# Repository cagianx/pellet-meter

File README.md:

# pellet-meter

Sensore di livello del pellet a batteria, per stufe. Misura con un sensore ToF
laser la distanza tra il coperchio e la superficie del pellet nella tramoggia,
e la trasmette a Home Assistant via **BLE advertising in formato BTHome v2**,
insieme allo stato della batteria.

Nessuna connessione BLE, nessun Wi-Fi, nessuna integrazione custom: il
dispositivo si risveglia, misura, trasmette un pacchetto di advertising e
torna in deep sleep. Home Assistant lo riconosce da solo.

## Hardware

| | |
|---|---|
| MCU | Seeed XIAO ESP32C6 — USB-C e caricabatterie LiPo integrati, BLE 5 |
| Sensore | VL53L1X (ToF laser, I²C) — misura da ~4 cm, niente zona cieca |
| Alimentazione | LiPo 3,7 V 1000 mAh con circuito di protezione |
| Radio | BLE advertising, BTHome v2 |

Risveglio ogni **10 minuti**. Consumo stimato **~1,3 mAh al giorno**, cioe'
oltre un anno di autonomia teorica — a quel punto conta piu' l'autoscarica
della batteria che il dispositivo. E' una stima: la misura sul banco e'
ancora da fare.

## Stato

| | |
|---|---|
| Schema elettrico | fatto — ERC pulito, netlist verificata; disposizione da curare |
| Firmware | scheletro ESP-IDF che compila, switch RF; misura e BTHome da scrivere |
| Contenitore 3D | modello OpenSCAD parametrico, quote verificate; si incolla sotto il coperchio della tramoggia, quindi capovolto |
| Configurazione Home Assistant | da fare |

Il repo fornisce **il progetto**, non la realizzazione: schema, firmware,
modello del contenitore e configurazione di Home Assistant. Comprare,
saldare, stampare e installare sono attivita' di chi costruisce.

La calibrazione (distanza ↔ percentuale di riempimento) si fa **in Home
Assistant**, non nel firmware: ricalibrare non richiede un reflash.

## Documentazione

Il sito completo — decisioni di progetto, hardware, collegamenti, formato del
pacchetto BTHome, configurazione di Home Assistant — e' pubblicato qui:

**https://cagianx.github.io/pellet-meter/**

Per lavorare sul repo, vedi [CLAUDE.md](CLAUDE.md): contiene i comandi di
verifica e le trappole del formato KiCad incontrate durante lo sviluppo.

## Struttura

```
kicad/        progetto KiCad 10 (schema, librerie di progetto, strumenti)
firmware/     progetto ESP-IDF (C17, target esp32c6)
enclosure/    contenitore parametrico OpenSCAD
tools/        render.sh — immagini per il sito e il README
docs/         sorgenti del sito di documentazione
```

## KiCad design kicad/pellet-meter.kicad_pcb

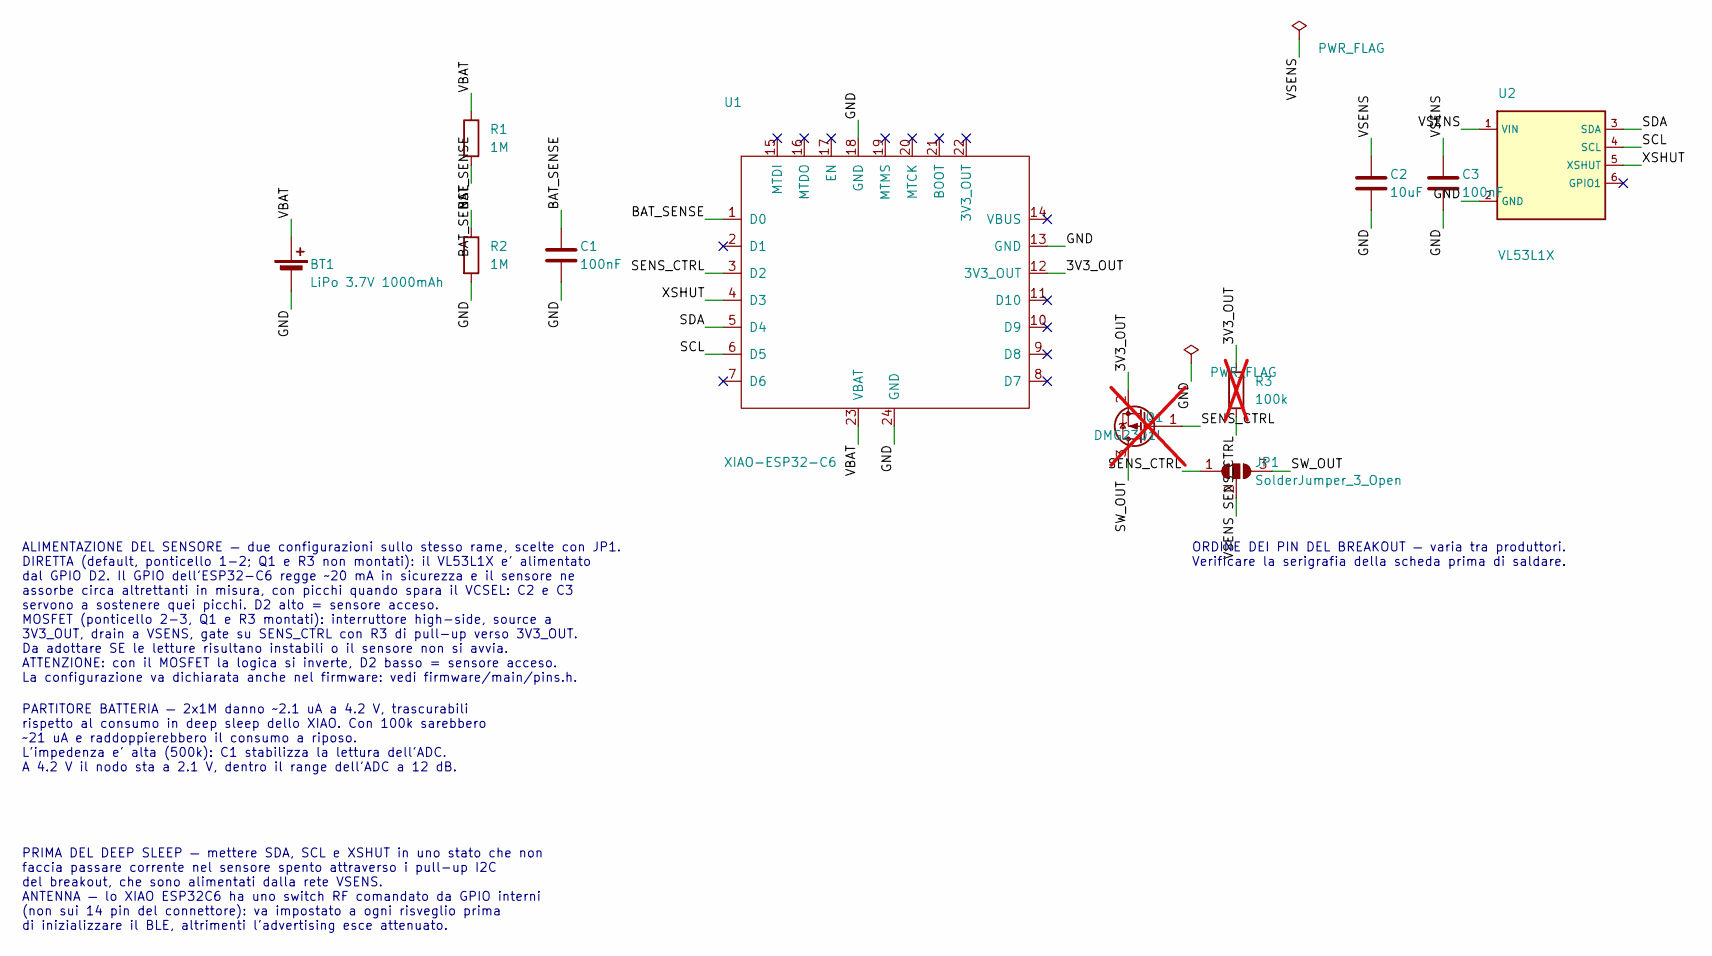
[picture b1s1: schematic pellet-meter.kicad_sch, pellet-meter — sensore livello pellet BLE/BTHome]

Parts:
BT1: LiPo 3.7V 1000mAh; PinHeader_1x02_P2.54mm_Vertical
C1, C3: 100nF; C_Disc_D5.0mm_W2.5mm_P5.00mm
C2: 10uF; CP_Radial_D5.0mm_P2.00mm
JP1: SolderJumper_3_Open; SolderJumper-3_P1.3mm_Open_Pad1.0x1.5mm_NumberLabels
Q1: DMG2301L; SOT-23; not fitted
R1, R2: 1M; R_Axial_DIN0207_L6.3mm_D2.5mm_P7.62mm_Horizontal
R3: 100k; R_Axial_DIN0207_L6.3mm_D2.5mm_P7.62mm_Horizontal; not fitted
U1: XIAO-ESP32-C6; XIAO-ESP32-C6-DIP
U2: VL53L1X; PinHeader_1x06_P2.54mm_Vertical

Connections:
/3V3_OUT: Q1.2 (S), R3.1, U1.12 (3V3_OUT)
/BAT_SENSE: C1.1, R1.2, R2.1, U1.1 (D0)
/GND: BT1.2 (-), C1.2, C2.2, C3.2, R2.2, U1.13 (GND), U1.18 (GND), U1.24 (GND), U2.2 (GND)
/SCL: U1.6 (D5), U2.4 (SCL)
/SDA: U1.5 (D4), U2.3 (SDA)
/SENS_CTRL: JP1.1 (A), Q1.1 (G), R3.2, U1.3 (D2)
/SW_OUT: JP1.3 (B), Q1.3 (D)
/VBAT: BT1.1 (+), R1.1, U1.23 (VBAT)
/VSENS: C2.1, C3.1, JP1.2 (C), U2.1 (VIN)
/XSHUT: U1.4 (D3), U2.5 (XSHUT)

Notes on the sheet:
ALIMENTAZIONE DEL SENSORE — due configurazioni sullo stesso rame, scelte con JP1. DIRETTA (default, ponticello 1-2; Q1 e R3 non montati): il VL53L1X e' alimentato dal GPIO D2. Il GPIO dell'ESP32-C6 regge ~20 mA in sicurezza e il sensore ne assorbe circa altrettanti in misura, con picchi quando spar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
PARTITORE BATTERIA — 2x1M danno ~2.1 uA a 4.2 V, trascurabili rispetto al consumo in deep sleep dello XIAO. Con 100k sarebbero ~21 uA e raddoppierebbero il consumo a riposo. L'impedenza e' alta (500k): C1 stabilizza la lettura dell'ADC. A 4.2 V il nodo sta a 2.1 V, dentro il range dell'ADC a 12 dB.
PRIMA DEL DEEP SLEEP — mettere SDA, SCL e XSHUT in uno stato che non faccia passare corrente nel sensore spento attraverso i pull-up I2C del breakout, che sono alimentati dalla rete VSENS. ANTENNA — lo XIAO ESP32C6 ha uno switch RF comandato da GPIO interni (non sui 14 pin del connettore): va impos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
ORDINE DEI PIN DEL BREAKOUT — varia tra produttori. Verificare la serigrafia della scheda prima di saldare.

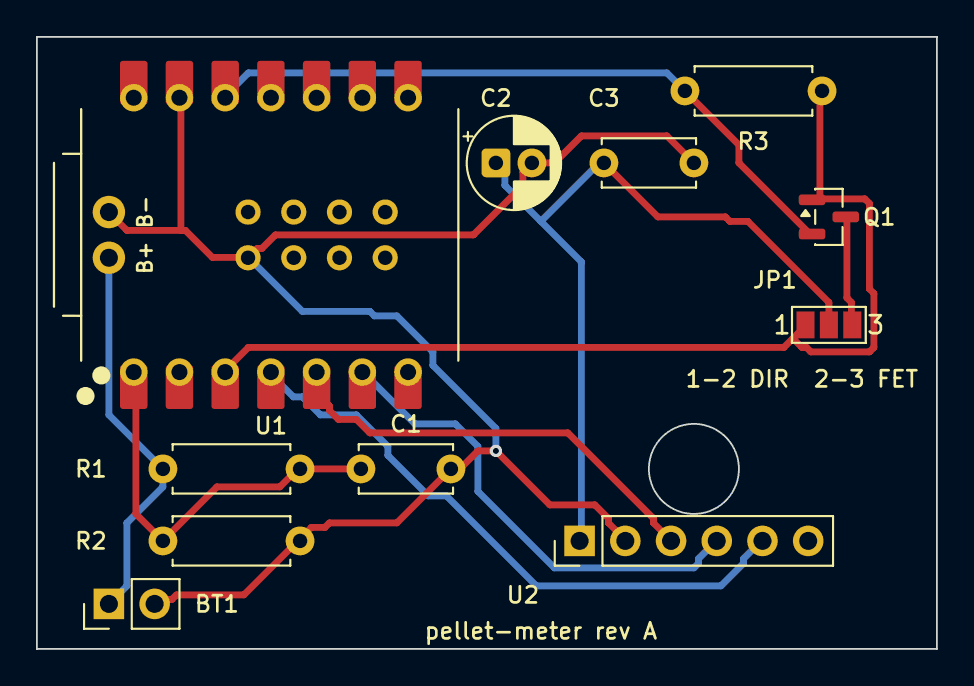
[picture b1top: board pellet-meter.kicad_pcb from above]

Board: 2 copper layers, 50.0 x 34.0 mm, 11 parts (0 on the bottom side), 10 nets.

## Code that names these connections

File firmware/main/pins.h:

// Mappa dei pin. Lo XIAO ESP32C6 stampa sulla scheda i nomi D0..D10, che
// non sono i numeri di GPIO: tradurli a mano in ogni file e' il modo di
// sbagliarne uno. Qui stanno entrambi i nomi, e questa e' l'unica tabella.
//
// Corrispondenza D -> GPIO dal wiki Seeed del XIAO ESP32C6; le reti sono
// quelle dello schema in kicad/pellet-meter.kicad_sch.

#pragma once

#include "driver/gpio.h"
#include "hal/adc_types.h"

// --- Reti dello schema ------------------------------------------------------

// SENS_CTRL: il pin che comanda l'alimentazione del breakout VL53L1X.
#define PIN_SENS_CTRL GPIO_NUM_2 // D2

// Come e' alimentato il sensore. Sul PCB le due configurazioni convivono e
// si scelgono col ponticello JP1 (1-2 diretta, 2-3 a MOSFET); su millefori
// c'e' solo la diretta.
//
//   0  diretta: D2 alimenta il breakout. ALTO = acceso.
//   1  MOSFET:  D2 pilota il gate di Q1, P-MOSFET high-side. BASSO = acceso.
//
// FRA LE DUE LA LOGICA SI INVERTE. E' una scelta esplicita a compile time
// proprio per questo: montare Q1 e dimenticarsene produce un sensore che
// non si accende mai, e sul banco sembra un sensore guasto. Il default e'
// allineato al default del rame, cioe' la configurazione gia' verificata.
#ifndef SENSORE_CON_MOSFET
#define SENSORE_CON_MOSFET 0
#endif

// Livello da mettere su SENS_CTRL per accendere il sensore.
#define SENS_CTRL_ACCESO (SENSORE_CON_MOSFET ? 0 : 1)

#define PIN_SDA   GPIO_NUM_22 // D4
#define PIN_SCL   GPIO_NUM_23 // D5
#define PIN_XSHUT GPIO_NUM_21 // D3

// BAT_SENSE: nodo del partitore 2x1 MOhm, con C1 da 100 nF.
#define PIN_BAT_SENSE GPIO_NUM_0 // D0

// GPIO0 e' ADC1_CH0 sull'ESP32-C6. Il canale va tenuto in coppia col pin:
// l'ADC non si programma per numero di GPIO.
#define ADC_BAT_UNIT    ADC_UNIT_1
#define ADC_BAT_CHANNEL ADC_CHANNEL_0

// --- Switch RF dell'antenna ------------------------------------------------
//
// Questi due GPIO non sono esposti sui 14 pin del connettore, quindi non
// compaiono sullo schema: esistono solo nel firmware.
//
// Nessuno dei due conserva lo stato attraverso il deep sleep: GPIO14 non e'
// un LP/RTC GPIO (sull'ESP32-C6 lo sono solo GPIO0..GPIO7), e GPIO3, che lo
// e', torna comunque al default se non si abilita l'hold. Vanno riscritti a
// OGNI risveglio, altrimenti il comando dello switch resta a mezz'aria.

#define PIN_RF_SWITCH_EN GPIO_NUM_3  // basso = controllo dello switch attivo
#define PIN_RF_ANT_SEL   GPIO_NUM_14 // basso = antenna ceramica integrata,
                                     // alto = connettore esterno

// Usiamo l'antenna integrata: il dispositivo sta nel contenitore, senza
// connettore U.FL montato.
#define RF_ANT_SEL_LEVEL 0
